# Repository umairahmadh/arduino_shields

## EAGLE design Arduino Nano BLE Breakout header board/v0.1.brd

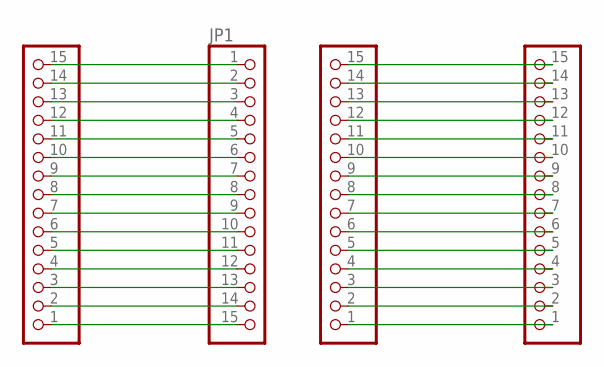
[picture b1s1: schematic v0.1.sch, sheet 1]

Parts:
JP1, JP2, JP3, JP4: PINHD-1X15-CASTELLATED; 1X15-CASTELL

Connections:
unnamed: JP1.1, JP2.15
unnamed: JP1.2, JP2.14
unnamed: JP1.3, JP2.13
unnamed: JP1.4, JP2.12
unnamed: JP1.5, JP2.11
unnamed: JP1.6, JP2.10
unnamed: JP1.7, JP2.9
unnamed: JP1.8, JP2.8
unnamed: JP1.9, JP2.7
unnamed: JP1.10, JP2.6
unnamed: JP1.11, JP2.5
unnamed: JP1.12, JP2.4
unnamed: JP1.13, JP2.3
unnamed: JP1.14, JP2.2
unnamed: JP1.15, JP2.1
unnamed: JP3.1, JP4.1
unnamed: JP3.2, JP4.2
unnamed: JP3.3, JP4.3
unnamed: JP3.4, JP4.4
unnamed: JP3.5, JP4.5
unnamed: JP3.6, JP4.6
unnamed: JP3.7, JP4.7
unnamed: JP3.8, JP4.8
unnamed: JP3.9, JP4.9
unnamed: JP3.10, JP4.10
unnamed: JP3.11, JP4.11
unnamed: JP3.12, JP4.12
unnamed: JP3.13, JP4.13
unnamed: JP3.14, JP4.14
unnamed: JP3.15, JP4.15

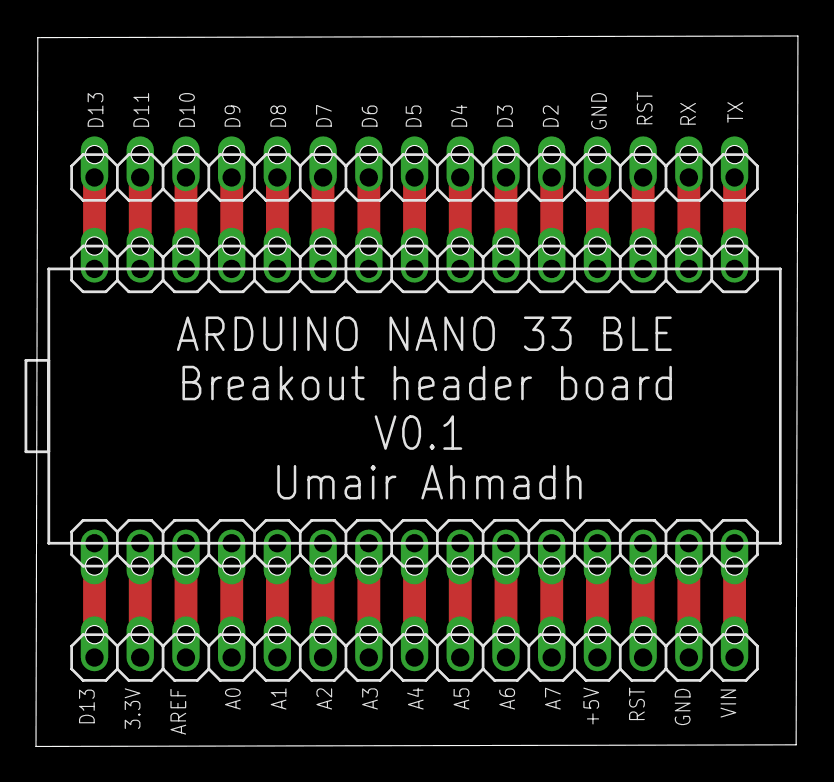
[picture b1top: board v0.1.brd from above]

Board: 2 copper layers, 42.3 x 39.5 mm, 4 parts (0 on the bottom side), 30 nets.

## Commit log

2020-03-25 Initial commit.

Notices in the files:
parts and their libraries:
Arduino-connectors: Copyright (c) 2016-2017 Arduino LLC.  All right reserved.
